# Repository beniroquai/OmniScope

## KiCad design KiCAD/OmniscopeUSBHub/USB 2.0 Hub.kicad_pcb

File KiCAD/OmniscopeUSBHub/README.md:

# SL2.1A Type-C Hub

Based on: https://github.com/Hugoyhu/SL2.1A-Type-C-Hub

A simple 4-port USB2 hub based on the SL2.1A design.
This board is designed in KiCAD v7! It is based off an earlier [2021 design](https://github.com/Hugoyhu/Hack-Club-Zephyr-USB-Hub) with USB-A outputs.

This revises the board to provide USB2 Type-C outputs. By default, the schematic provides circuitry for default USB power (500mA) but resistor values can be changed to provide higher output current if available through external power.

These boards have been tested and built with OSHPark After Dark service.

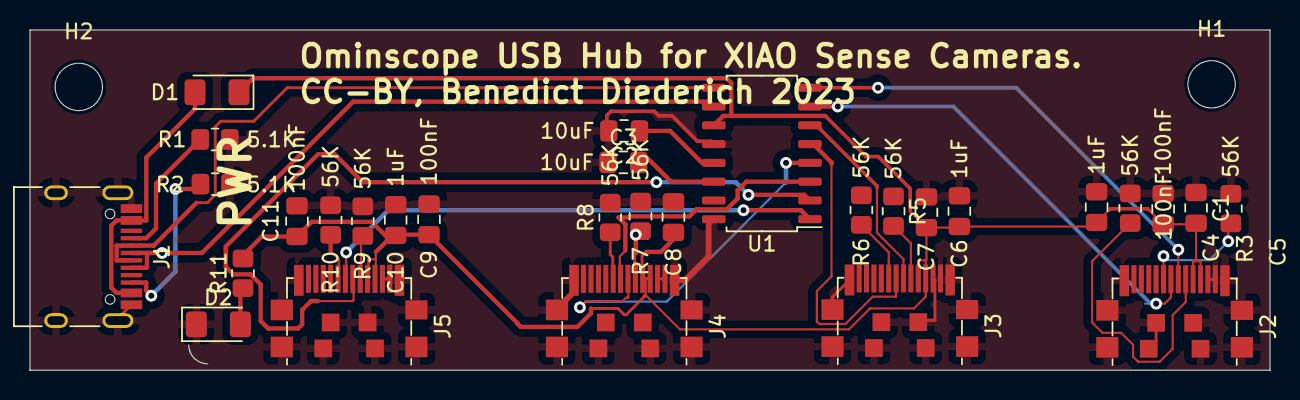
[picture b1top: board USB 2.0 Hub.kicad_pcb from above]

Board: 2 copper layers, 83.8 x 23.0 mm, 32 parts (0 on the bottom side), 26 nets.

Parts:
C1, C5, C7, C9, C11: 100nF; C_0805_2012Metric_Pad1.18x1.45mm_HandSolder
C2, C3: 10uF; C_0805_2012Metric_Pad1.18x1.45mm_HandSolder
C4, C6, C8, C10: 1uF; C_0805_2012Metric_Pad1.18x1.45mm_HandSolder
D1: SD1206T020S1R0; D_1206_3216Metric_Pad1.42x1.75mm_HandSolder
D2: LED_Small; LED_1206_3216Metric_Pad1.42x1.75mm_HandSolder
H1, H2: MountingHole; MountingHole_3.2mm_M3_ISO14580
J1: USB_C_Receptacle_USB2.0; USB_C_Receptacle_HRO_TYPE-C-31-M-12
J2, J3, J4, J5: USB_C_Receptacle_USB2.0; USB_C_Plug_UTC009-C12
R1, R2: 5.1K; R_0805_2012Metric_Pad1.20x1.40mm_HandSolder
R3, R4, R5, R6, R7, R8, R9, R10: 56K; R_0805_2012Metric_Pad1.20x1.40mm_HandSolder
R11: 100; R_0805_2012Metric_Pad1.20x1.40mm_HandSolder
U1: SL2.1A; SOIC-16_4.55x10.3mm_P1.27mm

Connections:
/D1+: J2.A6 (D+), U1.8 (DP1)
/D1-: J2.A7 (D-), U1.7 (DM1)
/D2+: J3.A6 (D+), U1.6 (DP2)
/D2-: J3.A7 (D-), U1.5 (DM2)
/D3+: J4.A6 (D+), U1.4 (DP3)
/D3-: J4.A7 (D-), U1.3 (DM3)
/D4+: J5.A6 (D+), U1.2 (DP4)
/D4-: J5.A7 (D-), U1.1 (DM4)
/D+: J1.A6 (D+), J1.B6 (D+), U1.10 (UDP)
/D-: J1.A7 (D-), J1.B7 (D-), U1.9 (UDM)
/VBUS: C1.2, C4.2, C5.2, C6.2, C7.2, C8.2, C9.2, C10.2, C11.2, D1.1 (K), J2.A4 (VBUS), J2.B9 (VBUS), J3.A4 (VBUS), J3.B9 (VBUS), J4.A4 (VBUS), J4.B9 (VBUS), J5.A4 (VBUS), J5.B9 (VBUS), R11.2, U1.11 (VCC5V)
GND: C1.1, C2.2, C3.1, C4.1, C5.1, C6.1, C7.1, C8.1, C9.1, C10.1, C11.1, D2.1 (K), J1.A1 (GND), J1.A12 (GND), J1.B1 (GND), J1.B12 (GND), J1.S1 (SHIELD), J2.A1 (GND), J2.B12 (GND), J2.S1 (SHIELD), J3.A1 (GND), J3.B12 (GND), J3.S1 (SHIELD), J4.A1 (GND), J4.B12 (GND), J4.S1 (SHIELD), J5.A1 (GND), J5.B12 (GND), J5.S1 (SHIELD), R1.1, R2.2, R3.1, R4.2, R5.1, R6.2, R7.1, R8.2, R9.1, R10.2, U1.12 (GND), U1.16 (XIN)
unnamed: D1.2 (A), J1.A4 (VBUS), J1.A9 (VBUS), J1.B4 (VBUS), J1.B9 (VBUS)
unnamed: D2.2 (A), R11.1
unnamed: J1.A5 (CC1), R1.2
unnamed: J1.B5 (CC2), R2.1
unnamed: J2.A5 (CC1), R3.2
unnamed: J2.B5 (CC2), R4.1
unnamed: J3.A5 (CC1), R5.2
unnamed: J3.B5 (CC2), R6.1
unnamed: J4.A5 (CC1), R7.2
unnamed: J4.B5 (CC2), R8.1
unnamed: J5.A5 (CC1), R9.2
unnamed: J5.B5 (CC2), R10.1
unnamed: C2.1, U1.13 (VDD3)
unnamed: C3.2, U1.14 (VDD18)

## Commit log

2021-09-15 Newest Version with two cameras 75cm
2021-09-23 Modified Single-sided Version for better Assembly
2021-09-23 First Prototype for a full assembly
2021-09-24 Updated ASsembly
2021-09-26 Updated it to an almost working solution
2021-09-28 adding focus
2021-10-01 Adding Python readout and updating CAD parts
2021-10-01 Adding image
2021-10-11 Updating the client and server code for the ESP32/PYthon; Updating printable STL files
2021-10-11 Updating Camera Bakcend
2021-10-11 Changing many camera-related settings on the esp
2021-10-11 further debugging
2021-10-11 Works, but without varying resolution
2021-10-12 Update streamer on ESP side to work faster
2021-10-12 Working Solution with Python Client and ESP32 Server
2021-10-12 Attempting to use Napari as the viewer - prototyping
2021-10-13 First prototype for visualizing multiple cameras in a grid (Matplotlib)
2021-10-13 Updating Omniscope CAD and the playground to work with multiple cameras in NAPARI
2022-06-03 Major update on code and assembly
2023-03-05 Adding the PCB
2023-04-19 Adding PCB for SD Card
2023-06-15 Adding latest CAD Drawings
2023-12-06 Adding USB Port Kicad

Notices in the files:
KiCAD/OmniscopeUSBHub/USB 2.0 Hub.kicad_pcb:
CC-BY, Benedict Diederich 2023
